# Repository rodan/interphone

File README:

MSP430F5510 based project that ties into the appartment interphone system. in this case it's an Electra IA01.
it allows the owner outside the building to open the door by following a pre-determined list of actions.

if config.h RADIO option (*) is defined then the door opening is triggered by the following actions:
 - call interphone number
 - wait 2s
 - send a radio signal to a receiver that is tied into the project. the receiver should pull P1.2 low on activation.
 - door opens if the signal was received in the defined time window
 If the radio option is not viable due to poor signal/noise ratio another scenario is implemented by deactivating the RADIO ifdef.
 - call interphone number
 - hang up and call again in the software predetermined timeframe
 - door opens

 the first scenario needs one 12v battery, a 12V one channel RC receiver and transmitter. a chronos watch could be used as the RC remote if the topology permits, see [1], [2]. current consumption is about 110uA@12V.
 the second scenario only needs one 3v 2032 Li cell. current consumption is about 1.4uA@3V. the pcb for this one is to be found in hardware/ip_simple.brd

Pinout:
 - P1.1 - 'ring' detector from interphone 'PX'
 - P1.2 - (optional) radio trigger
 - P1.4 - OPEN
 - P1.5 - TALK
 - P1.6 - (optional) power enable for radio rx system

(*) radio-related code removed

 homepage:        https://github.com/rodan/interphone
 author:          Petre Rodan <2b4eda@subdimension.ro>
 license:         GNU GPLv3
 parts of the code were originally forked from the openchronos-ng project [3]. 

 software requirements:

   msp430 toolchain

[1] http://www.ti.com/tool/ez430-chronos
[2] https://github.com/rodan/openchronos-rfsw
[3] http://openchronos-ng.sourceforge.net

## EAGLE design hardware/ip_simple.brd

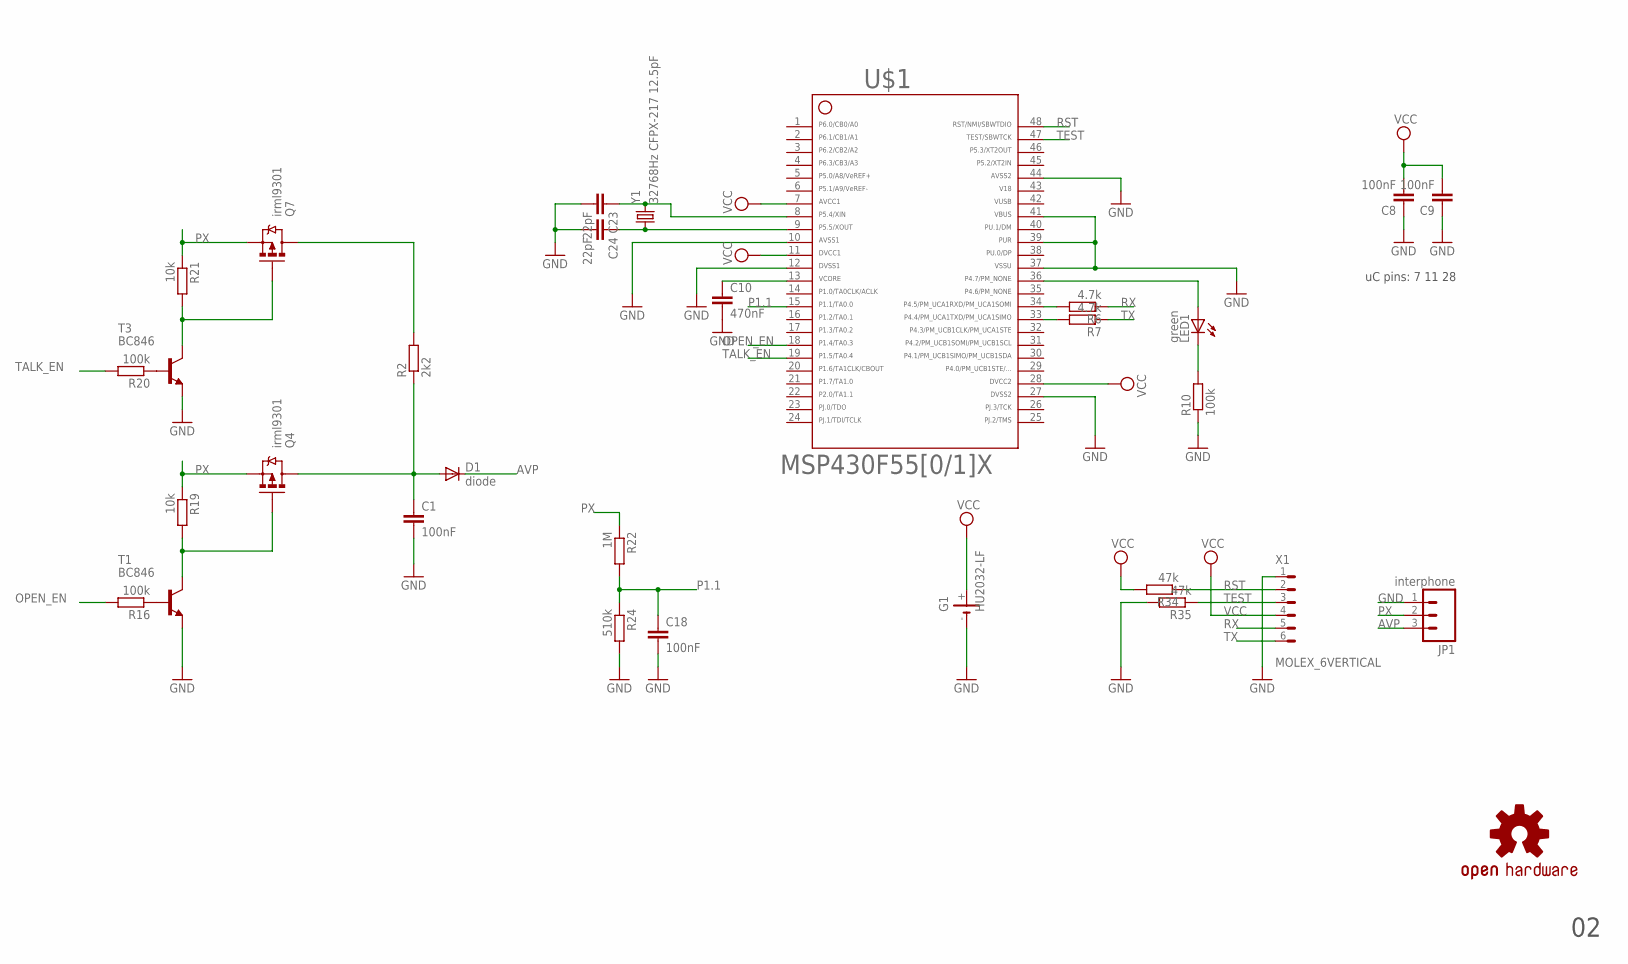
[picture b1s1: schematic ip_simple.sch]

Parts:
C1, C8, C9, C18: 100nF; C0805
C10: 470nF; C0805
C23, C24: 22pF; C0805
D1: diode; SMA-DIODE
G1: HU2032-LF
JP1: interphone; 1X03
LED1: green; CHIP-LED0805
Q4, Q7: irml9301; SOT23-3_POWER
R2: 2k2; R0805W
R6, R7: 4.7k; R0805W
R10, R16, R20: 100k; R0805W
R19, R21: 10k; R0805W
R22: 1M; R0805W
R24: 510k; R0805W
R34, R35: 47k; R0805W
T1, T3: BC846; SOT23
U$1: F55[0/1]X---PT48; PT48
U$7: OSHW-LOGOM; OSHW-LOGO-M
X1: MOLEX_6VERTICAL; 0530470610
Y1: 32768Hz CFPX-217 12.5pF; CRYSTAL-SMD-3.2X1.5

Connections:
42: U$1.42
43: U$1.43
46: U$1.46
AVP: D1.C, JP1.3
GND: C1.2, C8.1, C9.1, C10.2, C18.2, C23.2, C24.2, G1.-, JP1.1, R10.1, R24.2, R35.2, T1.2 (E), T3.2 (E), U$1.10, U$1.12, U$1.27, U$1.37, U$1.39, U$1.41, U$1.44, X1.1
LED: LED1.A, U$1.36
unnamed: LED1.C, R10.2
unnamed: R16.1, T1.1 (B)
unnamed: C1.1, D1.A, Q4.3 (D), R2.1
unnamed: Q7.3 (D), R2.2
unnamed: C10.1, U$1.13
unnamed: R6.2, U$1.34
unnamed: R7.2, U$1.33
unnamed: C24.1, U$1.9, Y1.P$1 (1)
unnamed: C23.1, U$1.8, Y1.P$2 (2)
unnamed: Q4.1 (G), R19.2, T1.3 (C)
unnamed: R20.1, T3.1 (B)
unnamed: Q7.1 (G), R21.2, T3.3 (C)
OPEN_EN: R16.2, U$1.18
P1.1: C18.1, R22.2, R24.1, U$1.15
PX: JP1.2, Q4.2 (S), Q7.2 (S), R19.1, R21.1, R22.1
RST: R34.1, U$1.48, X1.2
RX: R6.1, X1.5
TALK_EN: R20.2, U$1.19
TEST: R35.1, U$1.47, X1.3
TX: R7.1, X1.6
VCC: C8.2, C9.2, G1.+, R34.2, U$1.7, U$1.11, U$1.28, X1.4

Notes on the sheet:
uC pins: 7 11 28

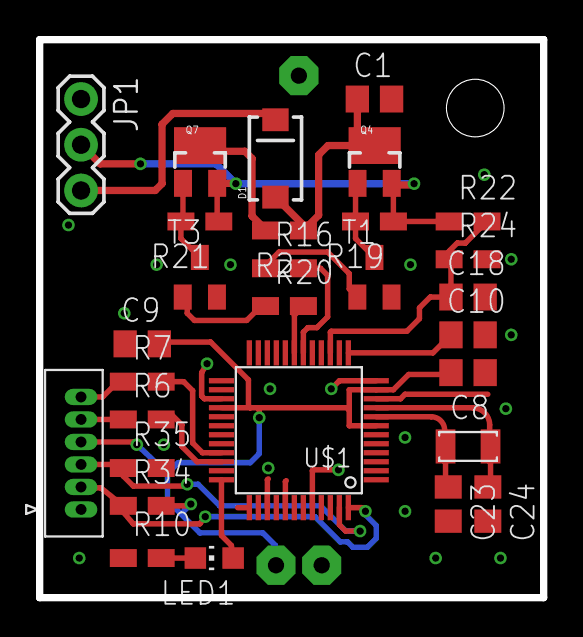
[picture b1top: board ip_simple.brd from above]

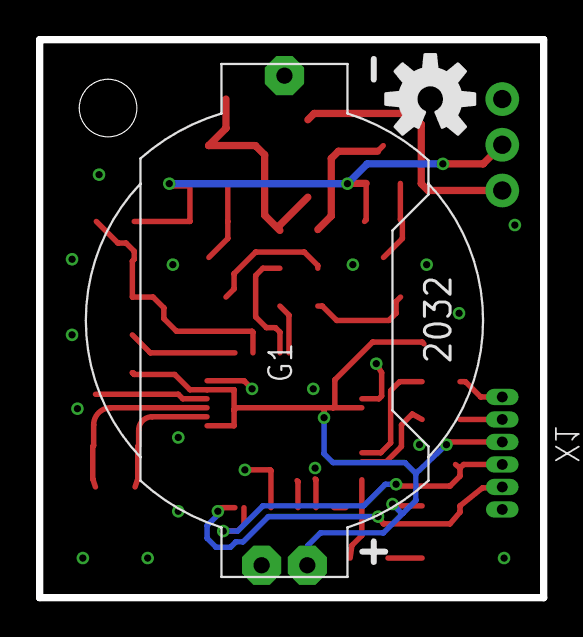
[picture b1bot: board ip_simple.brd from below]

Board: 2 copper layers, 28.0 x 31.0 mm, 31 parts (2 on the bottom side), 24 nets.

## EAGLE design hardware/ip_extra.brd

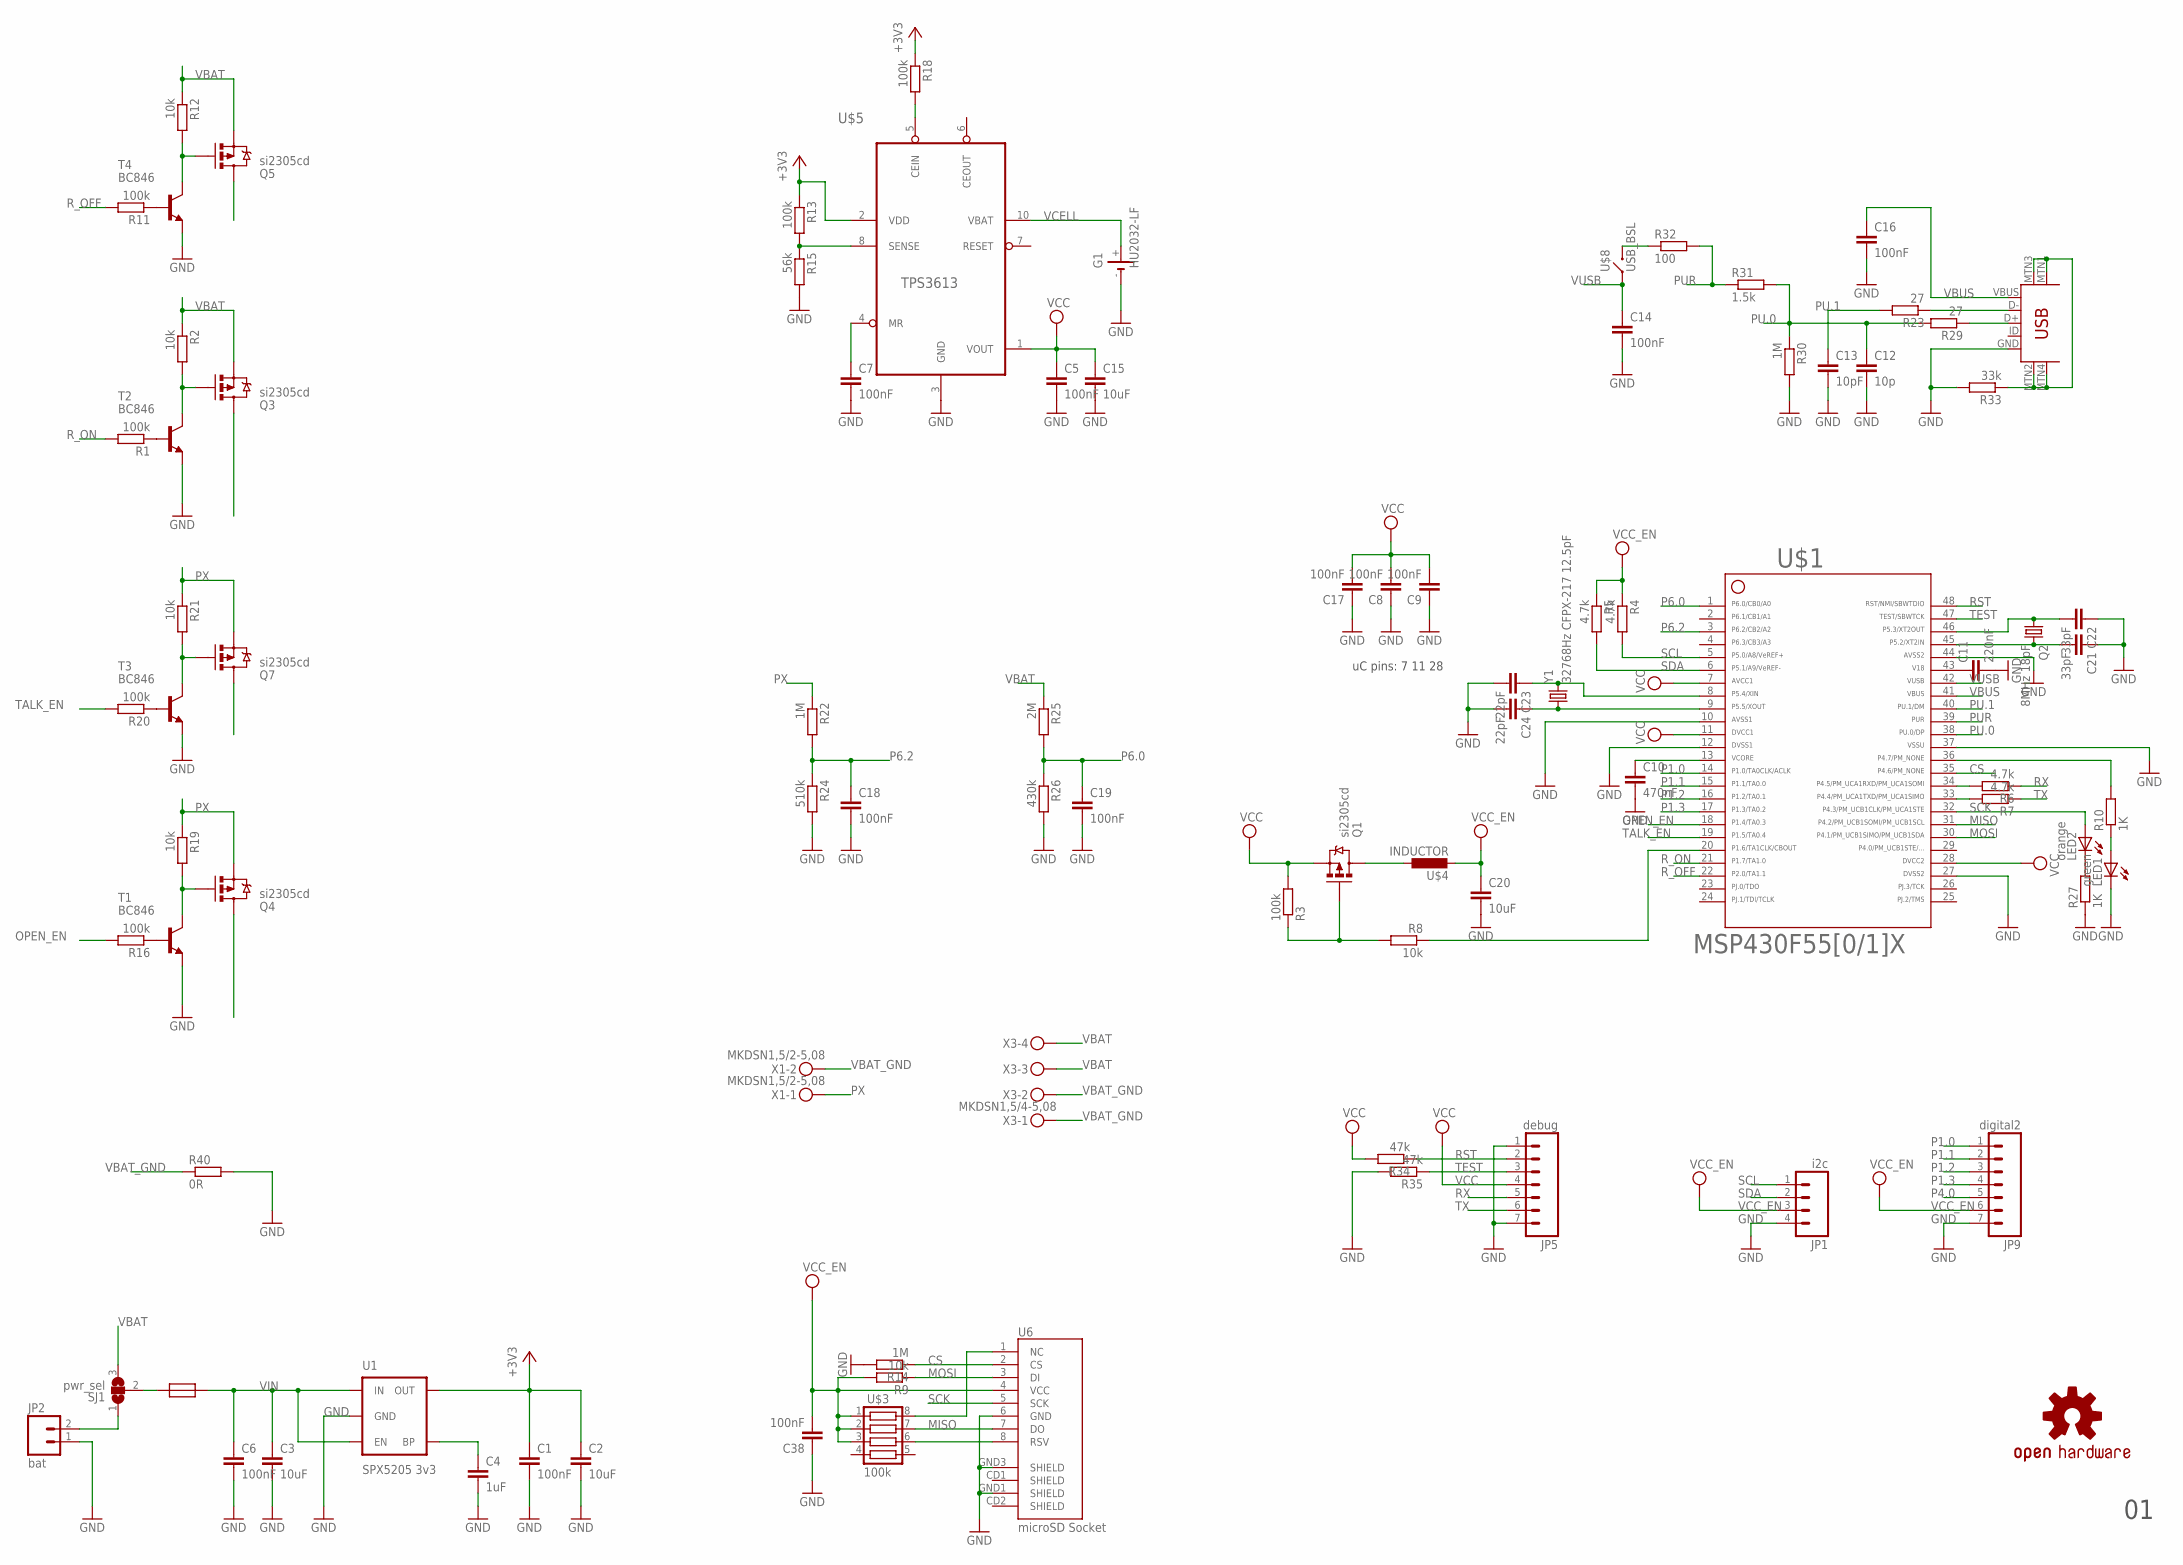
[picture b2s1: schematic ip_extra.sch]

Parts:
C1, C5, C6, C7, C8, C9, C14, C16, C17, C18, C19, C38: 100nF; C0805
C2, C3, C15, C20: 10uF; C1206
C4: 1uF; C0805
C10: 470nF; C0805
C11: 220nF; C0805
C12: 10p; C0805
C13: 10pF; C0805
C21, C22: 33pF; C0805
C23, C24: 22pF; C0805
G1: HU2032-LF
JP1: i2c; 1X04
JP2: bat; 1X02
JP5: debug; 1X07
JP9: digital2; 1X07
LED1: green; CHIP-LED0805
LED2: orange; CHIP-LED0805
Q1, Q3, Q4, Q5, Q7: si2305cd; SOT23-3_POWER
Q2: 8MHz 18pF; CRYSTAL_5X3.2
R1, R3, R11, R13, R16, R18, R20: 100k; R0805W
R2, R8, R9, R12, R19, R21: 10k; R0805W
R4, R5, R6, R7: 4.7k; R0805W
R10, R27: 1K; R0805W
R14, R22, R30: 1M; R0805W
R15: 56k; R0805W
R23, R29: 27; R0805W
R24: 510k; R0805W
R25: 2M; R0805W
R26: 430k; R0805W
R31: 1.5k; R0805W
R32: 100; R0805W
R33: 33k; R0805W
R34, R35: 47k; R0805W
R40: 0R; R0805W
SJ1: pwr_sel; SJ_2
T1, T2, T3, T4: BC846; SOT23
U1: SPX5205 3v3; SOT23-5
U6: microSD Socket; MICRO-SD-SOCKET-PP
U$1: F55[0/1]X---PT48; PT48
U$2: RESETTABLE; 1210
U$3: 100k; YC164
U$4: INDUCTOR; L0805W
U$5: TPS3613; MSOP_10P
U$6: USB-MINIB-5PIN; USB-MINIB
U$7: OSHW-LOGOM; OSHW-LOGO-M
U$8: USB_BSL; 6X3.5_TACTILE_SW
X1: MKDSN1,5/2-5,08
X3: MKDSN1,5/4-5,08
Y1: 32768Hz CFPX-217 12.5pF; CRYSTAL-SMD-3.2X1.5

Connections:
+3V3: C1.1, C2.1, R13.1, R18.1, U1.5 (OUT), U$5.2 (VDD)
CS: R14.1, U6.2 (CS), U$1.35
EN: R8.1, U$1.20
GND: C1.2, C2.2, C3.2, C4.2, C5.2, C6.2, C7.2, C8.1, C9.1, C10.2, C11.2, C12.2, C13.2, C14.2, C15.2, C16.2, C17.1, C18.2, C19.2, C20.2, C21.1, C22.1, C23.2, C24.2, C38.1, G1.-, JP1.4, JP2.1, JP5.1, JP5.7, JP9.7, LED1.C, R14.2, R15.2, R24.2, R26.2, R27.1, R30.2, R33.2, R35.2, R40.2, T1.2 (E), T2.2 (E), T3.2 (E), T4.2 (E), U1.2 (GND), U6.6 (GND), U6.GND1 (SHIELD), U6.GND3 (SHIELD), U$1.10, U$1.12, U$1.27, U$1.37, U$1.44, U$5.3 (GND), U$6.GND
LED: R10.2, U$1.36
MISO: U6.7 (DO), U$1.31, U$3.7
MOSI: R9.1, U6.3 (DI), U$1.30
unnamed: LED1.A, R10.1
unnamed: C4.1, U1.4 (BP)
unnamed: R16.1, T1.1 (B)
unnamed: U6.1 (NC), U$3.8
unnamed: C10.1, U$1.13
unnamed: C11.1, U$1.43
unnamed: R1.1, T2.1 (B)
unnamed: JP2.2, SJ1.1
unnamed: Q3.1 (G), R2.2, T2.3 (C)
unnamed: R6.2, U$1.34
unnamed: R7.2, U$1.33
unnamed: Q1.1 (G), R3.1, R8.2
unnamed: R11.1, T4.1 (B)
unnamed: Q5.1 (G), R12.2, T4.3 (C)
unnamed: C22.2, Q2.P$1 (1), U$1.46
unnamed: R13.2, R15.1, U$5.8 (SENSE)
unnamed: C7.1, U$5.4 (MR)
unnamed: R18.2, U$5.5 (CEIN)
unnamed: R29.1, U$6.D+
unnamed: C21.2, Q2.P$2 (2), U$1.45
unnamed: C24.1, U$1.9, Y1.P$1 (1)
unnamed: C23.1, U$1.8, Y1.P$2 (2)
unnamed: U6.8 (RSV), U$3.6
unnamed: Q4.1 (G), R19.2, T1.3 (C)
unnamed: R23.1, U$6.D-
unnamed: R20.1, T3.1 (B)
unnamed: Q7.1 (G), R21.2, T3.3 (C)
unnamed: R32.1, U$8.2
unnamed: R33.1, U$6.MTN1 (MTN2), U$6.MTN2 (MTN3), U$6.MTN3 (MTN1), U$6.MTN4
unnamed: Q1.3 (D), U$4.1
unnamed: LED2.C, R27.2
unnamed: SJ1.2, U$2.P$1
OPEN_EN: R16.2, U$1.18
P1.0: JP9.1, U$1.14
P1.1: JP9.2, U$1.15
P1.2: JP9.3, U$1.16
P1.3: JP9.4, U$1.17
P4.0: JP9.5
P6.0: C19.1, R25.2, R26.1, U$1.1
P6.2: C18.1, R22.2, R24.1, U$1.3
PU.0: C12.1, R29.2, R30.1, R31.2, U$1.38
PU.1: C13.1, R23.2, U$1.40
PUR: R31.1, R32.2, U$1.39
PX: Q4.2 (S), Q7.2 (S), R19.1, R21.1, R22.1, X1.1
RST: JP5.2, R34.1, U$1.48
RX: JP5.5, R6.1
R_OFF: R11.2, U$1.22
R_ON: R1.2, U$1.21
SCK: LED2.A, U6.5 (SCK), U$1.32
SCL: JP1.1, R4.2, U$1.5
SDA: JP1.2, R5.2, U$1.6
TALK_EN: R20.2, U$1.19
TEST: JP5.3, R35.1, U$1.47
TX: JP5.6, R7.1
VBAT: Q3.2 (S), Q5.2 (S), R2.1, R12.1, R25.1, SJ1.3, X3.3, X3.4
VBAT_GND: R40.1, X1.2, X3.1, X3.2
VBUS: C16.1, U$1.41, U$6.VBUS
VCC: C5.1, C8.2, C9.2, C15.1, C17.2, JP5.4, Q1.2 (S), R3.2, R34.2, U$1.7, U$1.11, U$1.28, U$5.1 (VOUT)
VCC_EN: C20.1, C38.2, JP1.3, JP9.6, R4.1, R5.1, R9.2, U6.4 (VCC), U$3.1, U$3.2, U$3.3, U$4.2
VCELL: G1.+, U$5.10 (VBAT)
VIN: C3.1, C6.1, U1.1 (IN), U1.3 (EN), U$2.P$2
VUSB: C14.1, U$1.42, U$8.1

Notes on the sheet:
uC pins: 7 11 28

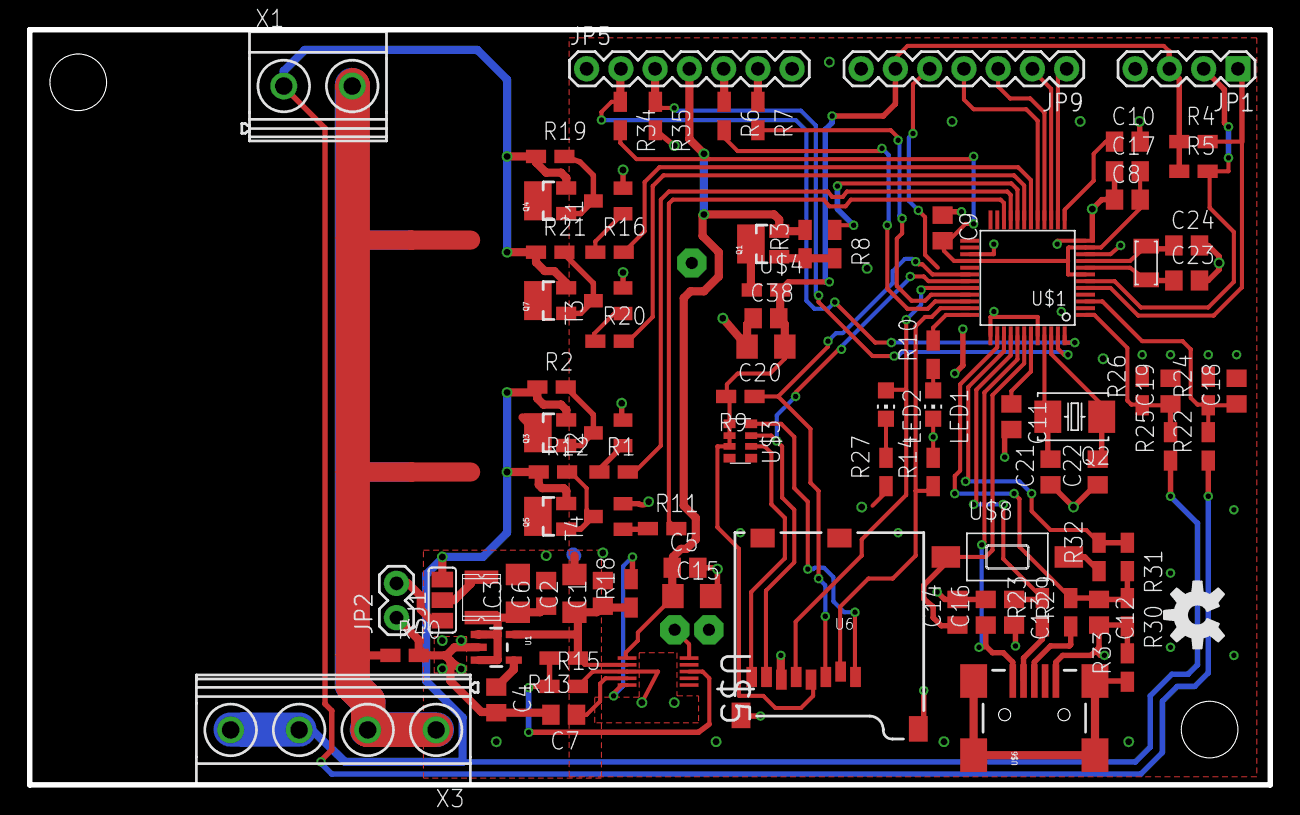
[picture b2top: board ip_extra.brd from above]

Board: 2 copper layers, 92.0 x 56.0 mm, 90 parts (1 on the bottom side), 68 nets.

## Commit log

2013-11-22 add sch+brd for the simple scenario
2013-11-22 add pinout
2013-11-22 sent to manufacturer
2013-11-24 fix ADC REFVSEL bug
2013-11-24 use reference libs
2013-12-20 fix wrong pin in README
2013-12-21 rev 2
2014-01-18 revision 2
2014-01-18 remove sleep fct
2014-01-18 cleanup CONFIG_DEBUG
2014-01-27 remove python scripts
2014-05-13 cleanup for unused pins
2015-08-27 python not needed as dependency
2018-09-01 email change
2018-12-13 change img location
2018-12-13 add pics

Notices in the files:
parts and their libraries:
SparkFun-Connectors: Licensing: CC v3.0 Share-Alike You are welcome to use this library for commercial purposes.
